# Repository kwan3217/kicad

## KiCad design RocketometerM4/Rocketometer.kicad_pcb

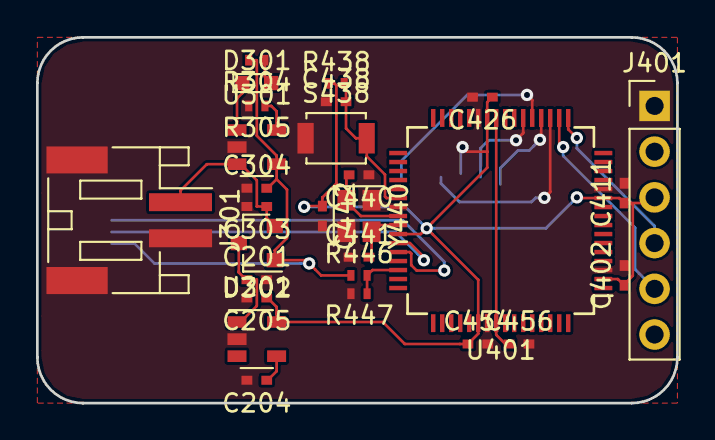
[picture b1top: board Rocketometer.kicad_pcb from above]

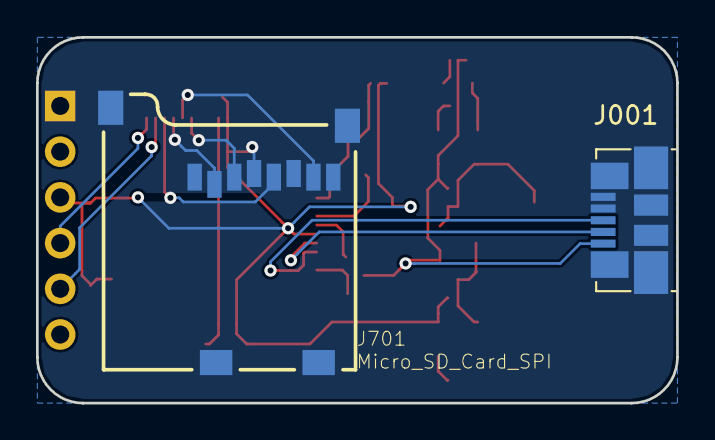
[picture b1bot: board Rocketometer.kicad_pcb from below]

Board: 2 copper layers, 35.6 x 20.3 mm, 30 parts (2 on the bottom side), 22 nets.

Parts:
C201, C205, C303, C304: 4.7uF; C_0402_NoSilk
C204, C402, C411, C426, C438, C442, C454: 100nF; C_0402_NoSilk
C440, C441: 22pF; C_0402_NoSilk
C456: 3.3uF; C_0402_NoSilk
D301: Yellow; LED_0603
D302: PMEG2005CT; SOT-23
J001: USB_OTG; USB_Micro-B_Molex_47346-0001
J301: Battery_Cell_Conn; JST_PH_S2B-PH-SM4-TB_02x2.00mm_Angled
J401: CONN_01X06; Pin_Header_Straight_1x06_Pitch2.54mm
J701: Micro_SD_Card_SPI; MICROSD-SOCKET-PP
R304, R305, R438, R446: 10k; R_0402_NoSilk
R447: 22k; R_0402_NoSilk
S438: SW_Push; SW_SPST_B3U-1000P
U201: MIC5319-3.3; SOT-23-5
U301: MCP73831; SOT-23-5
U401: TM4C1232; LQFP-64_10x10mm_Pitch0.5mm
Y440: Crystal_GND24; Crystal_SMD_2520-4pin_2.5x2.0mm

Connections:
+3V3: C205.1, C402.1, C411.1, C426.1, C442.1, C454.1, J401.3, J701.4, R438.1, U201.5, U401.2, U401.11, U401.26, U401.42, U401.54
/BYPASS: C204.1, U201.4
/CS_SD: J701.2, U401.20
/D+: J001.3, U401.44
/D-: J001.2, U401.43
/MISO0: J701.7, U401.21
/MOSI0: J701.3, U401.22
/OSC0: C440.2, U401.40, Y440.1
/OSC1: C441.2, U401.41, Y440.3
/PROG: R305.1, U301.5
/RESET: C438.2, R438.2, S438.2, U401.38
/RX0: J401.4, U401.17
/SCK0: J701.5, U401.19
/STAT+: D301.2, R304.1
/STAT-: D301.1, U301.1
/TX0: J401.5, U401.18
/VBUS+: C304.2, D302.1, J001.1, R304.2, R446.1, U301.4
/VBUS-: R446.2, R447.1, U401.46
/VDDC: C456.1, U401.25, U401.56
/VIN: C201.1, D302.3, U201.1
/VLIPO: C303.1, D302.2, J301.2, U301.3
GND: C201.2, C204.2, C205.2, C303.2, C304.1, C402.2, C411.2, C426.2, C438.1, C440.1, C441.1, C442.2, C454.2, C456.2, J001.4, J001.5, J001.6, J301.1, J301.3, J301.4, J401.1, J701.6, R305.2, R447.2, S438.1, U201.2, U301.2, U401.3, U401.12, U401.27, U401.39, U401.55, Y440.2, Y440.4

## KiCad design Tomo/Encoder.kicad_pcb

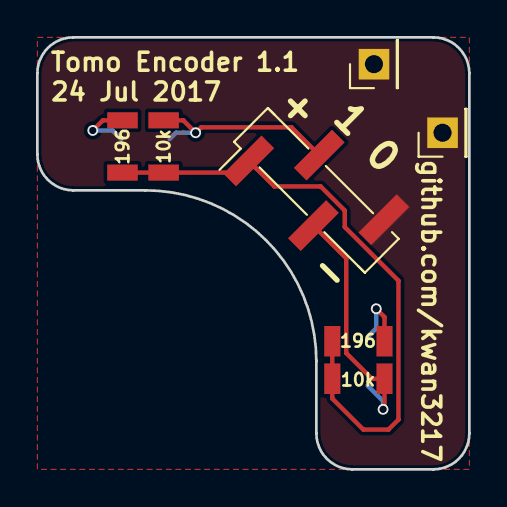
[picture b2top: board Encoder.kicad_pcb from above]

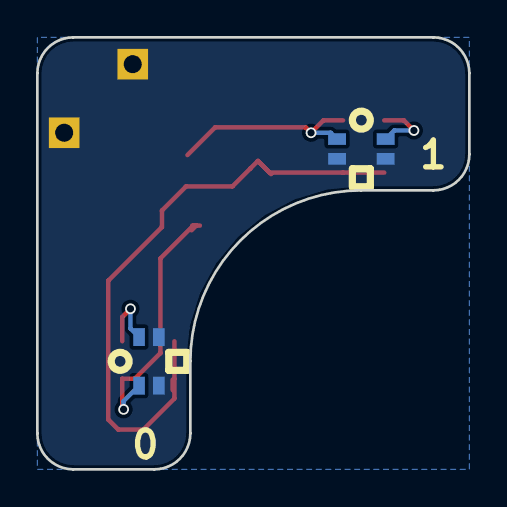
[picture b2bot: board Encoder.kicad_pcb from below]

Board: 2 copper layers, 24.0 x 24.0 mm, 9 parts (2 on the bottom side), 6 nets.

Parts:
J1: CONN_01X04; Pin_Header_Straight_1x04_Pitch2.54mm_SMD_Pin1Left
J201, J202: CONN_01X01; Pin_Header_Straight_1x01_Pitch2.54mm
R001, R101: 196; SMD_1206
R003, R103: 10k; SMD_1206
U000, U100: EE-SY199

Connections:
/D0: R001.2, U000.1
/D1: R101.2, U100.1
/ENC0: J1.3, R003.2, U000.3
/ENC1: J1.2, R103.2, U100.3
GND: J1.4, J201.1, J202.1, U000.2, U000.4, U100.2, U100.4
VCC: J1.1, R001.1, R003.1, R101.1, R103.1

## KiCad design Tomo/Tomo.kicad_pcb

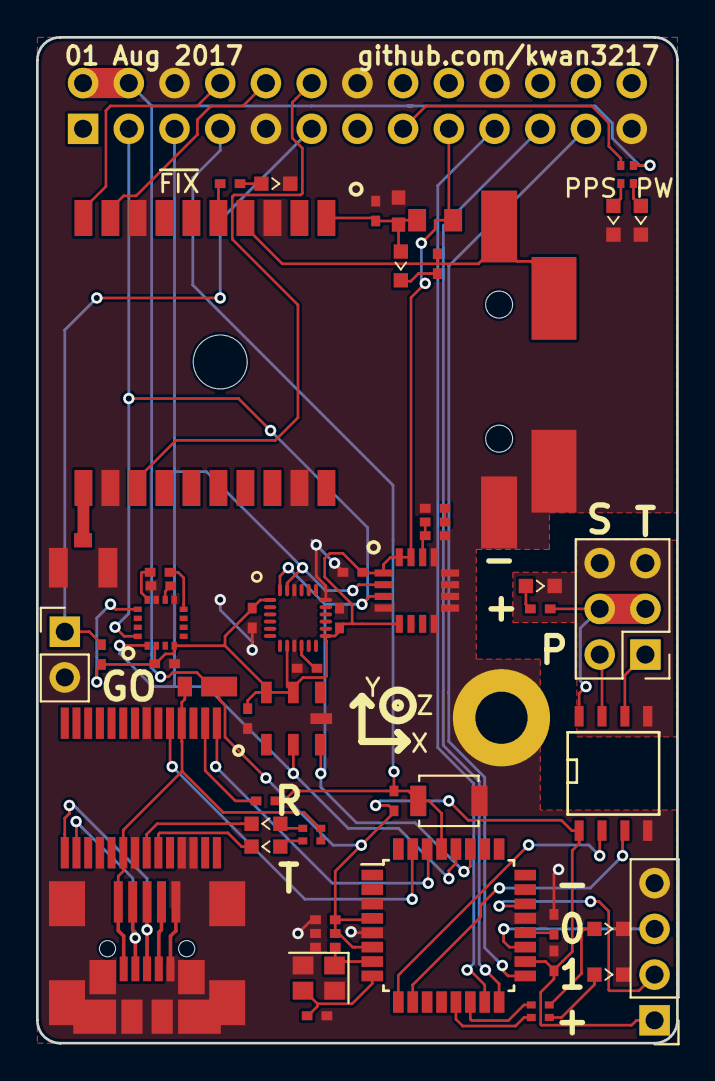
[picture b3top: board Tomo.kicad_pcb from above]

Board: 2 copper layers, 35.6 x 55.9 mm, 59 parts (1 on the bottom side), 54 nets.

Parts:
B604: Coin_Cell; CR1220-2
C002, C404, C406, C418, C420, C508, C510, C513, C601, C702, C802, C901: 100nF; SMD_0402
C407, C408: 22pF; SMD_0402
C603: 10uF; SMD_0603
C604: 220mF; Supercap
C708: 220nF; SMD_0402
C710: 4.7uF; SMD_0402
C913: 10nF; SMD_0402
C914: 470nF; SMD_0402
D001: MSS1P2; D_TUMD2
D022: BLUE; D_0603
D023, D122, D432, D613: RED; D_0603
D306, D401: GREEN; D_0603
D417: YELLOW; D_0603
D604: D_Schottky; D_0603
J001: USB_MICROB; USB_Double-B
J002: STANDOFF_GND; MountingHole_2.9mm_M2.5_Pad
J101: Raspberry_Pi_1; Socket_Strip_Straight_2x13_Pitch2.54mm
J102: CONN_01X02; Socket_Strip_Straight_1x02_Pitch2.54mm
J301: CONN_02X03; Pin_Header_Straight_2x03_Pitch2.54mm
J401: CONN_01X04; Pin_Header_Straight_1x04_Pitch2.54mm
L601: Ferrite; SMD_0805
R022, R122, R413: 680; R_Array_Convex_2x0402
R117, R429, R604, R914: 10k; SMD_0402
R306: 1.5k; SMD_0402
R613: 680; SMD_0402
R***: Axis
S429: SW_SPST; SW_SPST_B3U-1000P
U001: FT232RL; SSOP-28_5.3x10.2mm_Pitch0.65mm
U301: ADuM3221; SOIC-8-N
U401: ATMEGA328P-AU; LQFP-32_7x7mm_Pitch0.8mm
U501: MPU9250; QFN24_PAD
U601: FGPMMOPA6H
U701: HMC5883L
U801: BMP180
U901: L3G4200D
X611: uFL; U.FL
Y407: 16MHz; Crystal_SMD_2520-4pin_2.5x2.0mm

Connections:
+3V3: C508.2, C513.2, C702.2, C802.2, C901.2, J101.17, L601.1, R117.2, U501.1, U501.8, U501.13, U701.2, U701.4, U701.13, U801.2, U801.3, U901.1, U901.5, U901.15, U901.16
+5V: C404.1, C406.1, C418.1, D001.1, J101.2, J101.4, J401.1, R122.1, R429.1, U301.1, U401.4, U401.6, U401.18
+BATT: J301.3, J301.4, R306.1, U301.8
/Arduino/AREF: C420.1, U401.20
/Arduino/ATMega/XTAL1: C407.2, U401.7, Y407.1
/Arduino/ATMega/XTAL2: C408.2, U401.8, Y407.3
/Arduino/D0: U001.1, U401.30
/Arduino/D1: U001.5, U401.31
/Arduino/D+: J001.3, U001.15
/Arduino/D-: J001.2, U001.16
/Arduino/DTR: C002.1, U001.2
/Arduino/RXLED: D023.1, U001.22
/Arduino/RXLED+: D023.2, R022.3
/Arduino/TXLED: D022.1, U001.23
/Arduino/TXLED+: D022.2, R022.4
/Arduino/VBUS: D001.2, J001.1, R022.1, R022.2, U001.4, U001.20
/BATPWR+: D306.2, R306.2
/E0_ECHO: R413.2, U401.13
/E0_ECHO+: D432.2, R413.3
/E1_ECHO: R413.1, U401.14
/E1_ECHO+: D417.2, R413.4
/ENCODER0: J401.3, U401.19
/ENCODER1: J401.2, U401.22
/FIX: R613.1, U601.5
/FIX+: D613.2, R613.2
/GO_BTN: J101.11, J102.1, R117.1
/GPS_RX: J101.8, U601.10
/GPS_TX: J101.10, U601.9
/HMC5883L/C1: C710.2, U701.10
/HMC5883L/SETC: C708.2, U701.12
/HMC5883L/SETP: C708.1, U701.8
/L3G4200D/PLLFILT: C913.2, C914.2, U901.14
/L3G4200D/PLLFILT-: C914.1, R914.1
/MISO: J101.21, U401.16
/MOSI: J101.19, U401.15
/PPS: J101.12, U601.13
/PPS_ECHO: J101.15, R122.2
/PPS_ECHO+: D122.2, R122.3
/PWRLED+: D401.2, R122.4
/RESET: C002.2, J101.7, R429.2, S429.1, U401.29
/SCK: J101.23, U401.17
/SCL: J101.5, U401.28, U501.23, U701.1, U801.5, U901.2
/SDA: J101.3, U401.27, U501.24, U701.16, U801.6, U901.3
/STEER: U301.2, U401.9
/STEER_HI: J301.2, U301.7
/THROTTLE: U301.3, U401.10
/THROTTLE_HI: J301.1, U301.6
/UltimateGPS/ANT: U601.11, X611.3
/UltimateGPS/VBACKUP: B604.+, C604.1, R604.1, U601.4
/UltimateGPS/VBACKUP+: D604.1, R604.2
/UltimateGPS/VGPS: C601.2, C603.2, D604.2, L601.2, U601.1
GND: B604.-, C404.2, C406.2, C407.1, C408.1, C418.2, C420.2, C508.1, C510.1, C513.1, C601.1, C603.1, C604.2, C702.1, C710.1, C802.1, C901.1, C913.1, D122.1, D401.1, D417.1, D432.1, D613.1, J001.5, J001.6, J002.1, J101.6, J101.9, J101.14, J101.20, J101.25, J102.2, J401.4, R914.2, S429.2, U001.7, U001.18, U001.21, U001.25, U001.26, U301.4, U401.3, U401.5, U401.21, U501.9, U501.18, U501.22, U601.3, U601.8, U601.12, U601.19, U701.9, U701.11, U801.7, U901.4, U901.8, U901.9, U901.10, U901.11, U901.12, U901.13, X611.1, X611.2, Y407.2, Y407.4
GNDPWR: D306.1, J301.5, J301.6, U301.5
unnamed: C510.2, U501.10

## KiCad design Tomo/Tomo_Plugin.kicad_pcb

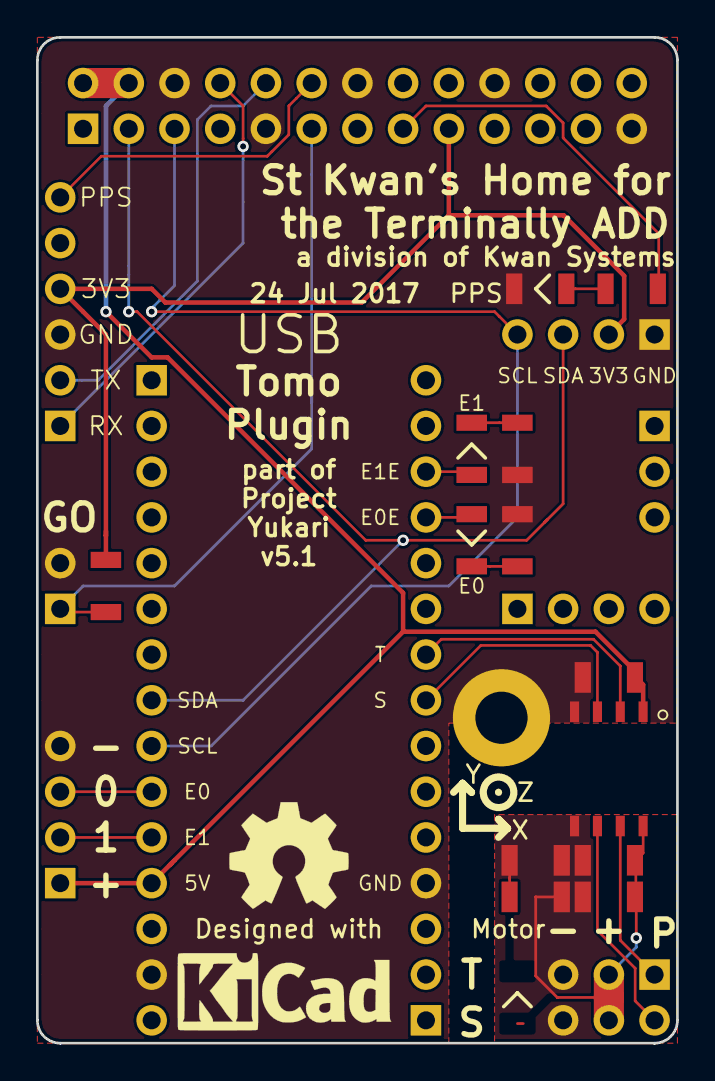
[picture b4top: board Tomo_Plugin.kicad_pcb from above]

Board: 2 copper layers, 35.6 x 55.9 mm, 26 parts (1 on the bottom side), 24 nets.

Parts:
C301, C305: 100nF; SMD_1206
C308: 10uF; SMD_1206
D112: RED; D_1206
D308: BLUE; D_1206
D409: GREEN; D_1206
D410: YELLOW; D_1206
J002: STANDOFF_GND; MountingHole_2.9mm_M2.5_Pad
J101: Raspberry_Pi_1; Socket_Strip_Straight_2x13_Pitch2.54mm
J102: CONN_01X02; Socket_Strip_Straight_1x02_Pitch2.54mm
J301: CONN_02X03; Pin_Header_Straight_2x03_Pitch2.54mm
J401, J501, J503: CONN_01X04; Pin_Header_Straight_1x04_Pitch2.54mm
J502: CONN_01X03; Pin_Header_Straight_1x03_Pitch2.54mm
J601: CONN_01X04; GPSFeatherWing
R112, R308, R409, R410: 220; SMD_1206
R117: 10k; SMD_1206
U001: Designed_With_Kicad; Symbol_KiCAD-Logo_CopperAndSilkScreenTop
U002: KwanSystems; KWAN_CIRCLE_soldermask
U301: ADuM3221; SOIC-8-N
U401: Arduino_Nano; ArduinoNano
U501: MPU9250; Axis

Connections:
+3V3: J101.17, J501.2, J601.4, R117.2
+5V: C301.1, J101.2, J101.4, J401.1, U301.1, U401.27
+BATT: C305.1, C308.1, D308.2, J301.3, J301.4, U301.8
/BATPWR-: D308.1, R308.1
/E0_ECHO: D409.2, U401.12
/E0_ECHO-: D409.1, R409.1
/E1_ECHO: D410.2, U401.13
/E1_ECHO-: D410.1, R410.1
/ENCODER0: J401.3, U401.25
/ENCODER1: J401.2, U401.26
/GO_BTN: J101.11, J102.1, R117.1
/GPS_RX: J101.8, J601.1
/GPS_TX: J101.10, J601.2
/PPS: J101.12, J601.6
/PPS_ECHO: J101.15, R112.1
/PPS_ECHO-: D112.2, R112.2
/SCL: J101.5, J501.4, U401.24
/SDA: J101.3, J501.3, U401.23
/STEER: U301.3, U401.8
/STEER_HI: J301.2, U301.6
/THROTTLE: U301.2, U401.9
/THROTTLE_HI: J301.1, U301.7
GND: C301.2, D112.1, J002.1, J101.6, J101.9, J101.14, J101.20, J101.25, J102.2, J401.4, J501.1, J601.3, R409.2, R410.2, U301.4, U401.4, U401.29
GNDPWR: C305.2, C308.2, J301.5, J301.6, R308.2, U301.5
